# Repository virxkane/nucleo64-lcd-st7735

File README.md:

# nucleo64-lcd-st7735
LCD shield for STM32 Nucleo-64 boards.

This shield is designed for connecting to STM32 Nucleo-64 boards via Arduino<sup>TM</sup> Uno V3.

**WARNING:** Although this shield can be connected to the Arduino<sup>TM</sup> UNO, it is incompatible in logic levels, so it is strictly forbidden to connect this way, otherwise this display will fail!

### Hardware
* The GMT177-01 module is used as a display and is compatible in size and pins. The display controller used is **ST7735**. The display data bus is connected to the hardware SPI. PWM can be used  to control the brightness of the screen backlight.
* Joystick K1-1504SA-03 and one button KLS7-TS6601 can be used for control. Both are connected to 3 General Purpose I/O ports via diodes.
* EEPROM memory M24C08 can be used to store user data. This IC is connected to the I2C hardware bus.
* Two LEDs are connected to ports A0(PA0) and A1(PA1).
* A separate button IT-1187-160GM-G is provided to reset the controller.

### Demo firmware
Two versions of the demo firmware have been written to work on the NUCLEO-F446RE and this shield, one using CMSIS, the other using HAL. Both are under BSD-3-Clause License.
* Using CMSIS: [nucleo-f446re-st7735spi-shield](https://github.com/virxkane/nucleo-f446re-st7735spi-shield)
* Using HAL: [nucleo-f446re-st7735spi-shield-hal](https://github.com/virxkane/nucleo-f446re-st7735spi-shield-hal)

#### Compare performance
| # |  bpp variant  | fill period, ms | transfer period, CMSIS, ms | transfer period, HAL, ms |
|---|---------------|--------|-----------|---------|
| 1 | fb=1, lcd=12  |     3  |      23   |    40   |
| 2 | fb=1, lcd=16  |     3  |      30   |    60   |
| 3 | fb=1, lcd=18  |     3  |      44   |    74   |
| 4 | fb=4, lcd=12  |     3  |      23   |    39   |
| 5 | fb=4, lcd=16  |     3  |      30   |    58   |
| 6 | fb=4, lcd=18  |     3  |      44   |    73   |
| 7 | fb=8, lcd=12  |     2  |      23   |    39   |
| 8 | fb=8, lcd=16  |     2  |      30   |    59   |
| 9 | fb=8, lcd=18  |     2  |      44   |    73   |
| 10 | fb=16, lcd=12 |    3  |      22   |    39   |
| 11 | fb=16, lcd=16 |    3  |      30   |    59   |
| 12 | fb=16, lcd=18 |    3  |      44   |    75   |
| 13 | fb=24, lcd=12 |    3  |      22   |    38   |
| 14 | fb=24, lcd=16 |    3  |      30   |    61   |
| 15 | fb=24, lcd=18 |    3  |      44   |    73   |

Where *fb* - frame buffer color depth, *lcd* - LCD module color depth, *fill period* - frame buffer fill period, *transfer period* - period of frame buffer transmission to LCD module.

Tests performed at SPI clock 11,25 Mbits/s.

### Schematic

### Some photo
Unfortunately, there are currently no rev.4 boards, and the existing rev.3 boards have a small error - the LEDs are connected to RX/D0(PA3) and TX/D1(PA2), which by default are connected to the USART of the on-board ST-LINK/V2-1 programmer. To correct this drawback, two wire are placed on the bottom of the board to ports A0(PA0) and A1(PA1). The boards of the rev.4 are free from this drawback.

#### Front view (rev.3)

#### Back view (rev.3)

#### Paired with NUCLEO-F446RE with running [demo](https://github.com/virxkane/nucleo-f446re-st7735spi-shield) (rev.3)

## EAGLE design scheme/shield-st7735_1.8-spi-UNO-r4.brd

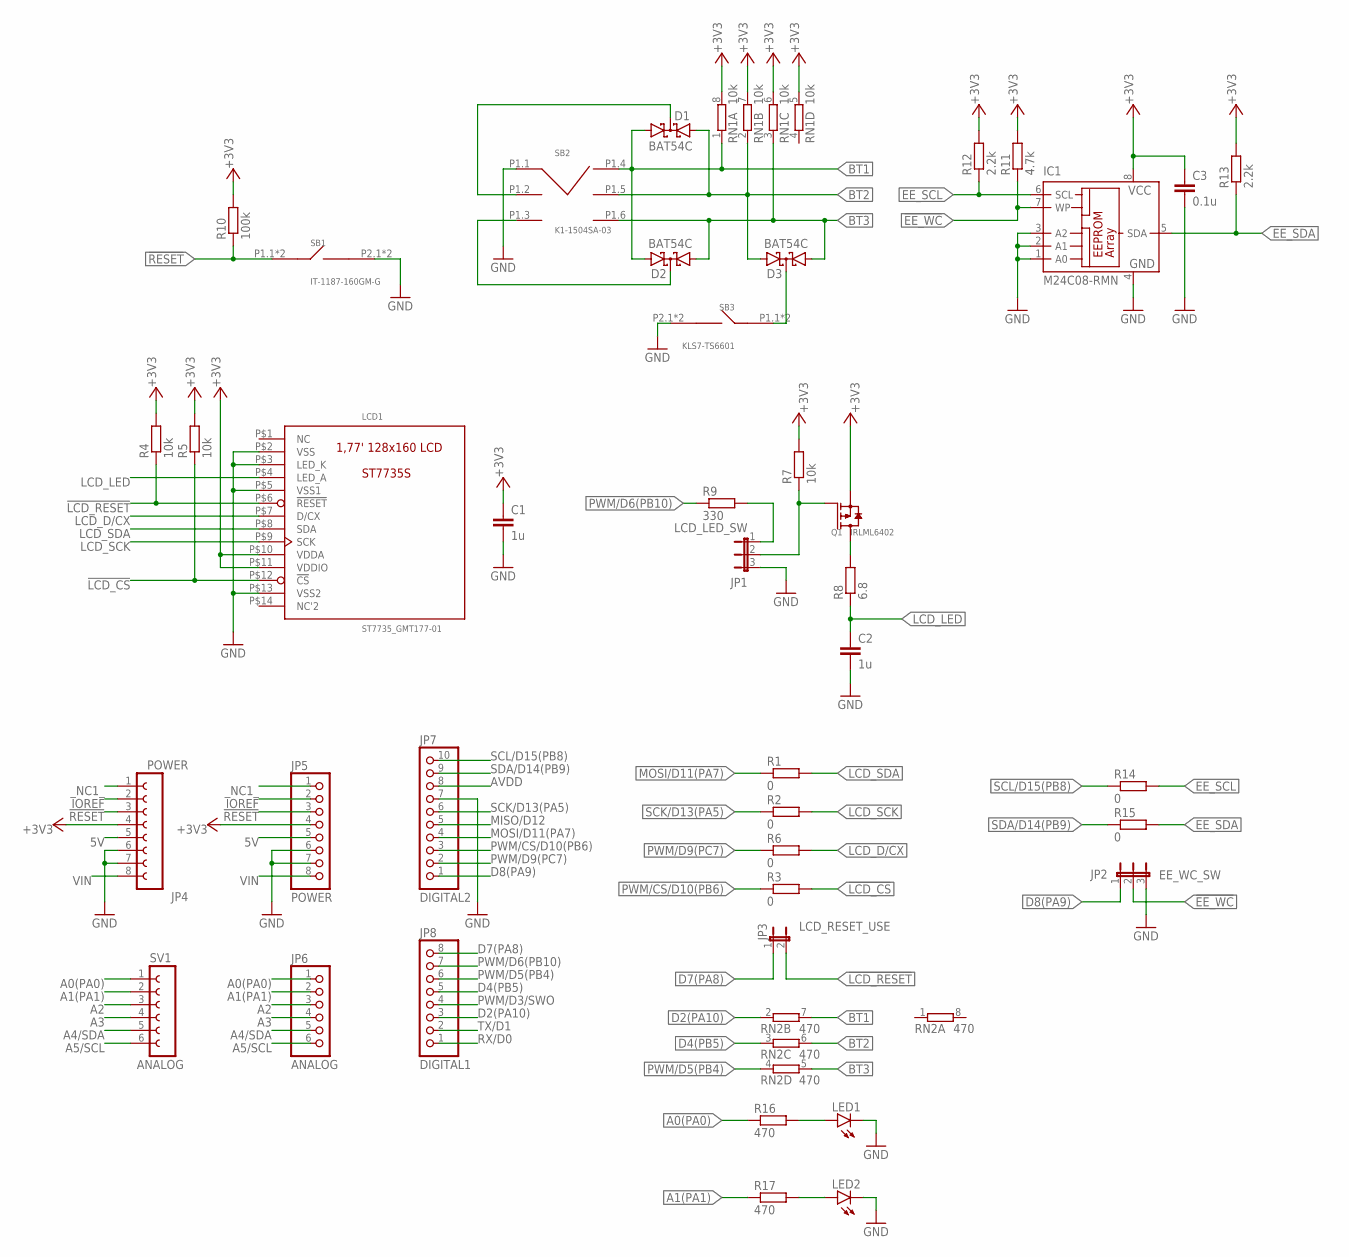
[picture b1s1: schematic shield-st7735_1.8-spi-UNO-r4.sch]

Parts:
C1, C2: 1u; C1206
C3: 0.1u; C1206
D1, D2, D3: BAT54C; SOT23
IC1: M24C08-RMN; SO-08
JP1: LCD_LED_SW; JP2
JP2: EE_WC_SW; JP2
JP3: LCD_RESET_USE; JP1
JP4: POWER; FE08
JP5: POWER; 1X08
JP6: ANALOG; 1X06
JP7: DIGITAL2; 1X10
JP8: DIGITAL1; 1X08
LCD1: ST7735_GMT177-01; GMT177-01
LED1, LED2: LEDCHIP-LED0805; CHIP-LED0805
Q1: IRLML6402; SOT23
R1, R2, R3, R6, R14, R15: 0; R1206
R4, R5, R7: 10k; R1206
R8: 6.8; R1206
R9: 330; R1206
R10: 100k; R1206
R11: 4.7k; R1206
R12, R13: 2.2k; R1206
R16, R17: 470; R1206
RN1: 10k; EXB38V
RN2: 470; EXB38V
SB1: IT-1187-160GM-G
SB2: K1-1504SA-03; K1-1504SA-3
SB3: KLS7-TS6601
SV1: ANALOG; FE06

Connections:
5V: JP4.5, JP5.5
!EE_WC!: IC1.7 (WP), JP2.2, R11.1
!LCD_CS!: LCD1.P$12 (!CS!), R3.2, R5.1
!LCD_RESET!: JP3.2, LCD1.P$6 (!RESET!), R4.1
!RESET!: JP4.3, JP5.3, R10.1, SB1.P1.1 (P1), SB1.P1.2 (P1)
+3V3: C1.1, C3.1, IC1.8 (VCC), JP4.4, JP5.4, LCD1.P$10 (VDDA), LCD1.P$11 (VDDIO), Q1.2 (S), R4.2, R5.2, R7.2, R10.2, R11.2, R12.2, R13.2, RN1.5 (2), RN1.6 (2), RN1.7 (2), RN1.8 (2)
A0(PA0): JP6.1, R16.1, SV1.1
A1(PA1): JP6.2, R17.1, SV1.2
A2: JP6.3, SV1.3
A3: JP6.4, SV1.4
A4/SDA: JP6.5, SV1.5
A5/SCL: JP6.6, SV1.6
AVDD: JP7.8
BT1: D1.1 (A1), D2.2 (A2), RN1.1, RN2.7 (2), SB2.P1.4 (P4)
BT2: D1.2 (A2), D3.2 (A2), RN1.2 (1), RN2.6 (2), SB2.P1.5 (P5)
BT3: D2.1 (A1), D3.1 (A1), RN1.3 (1), RN2.5 (2), SB2.P1.6 (P6)
D2(PA10): JP8.3, RN2.2 (1)
D4(PB5): JP8.5, RN2.3 (1)
D7(PA8): JP3.1, JP8.8
D8(PA9): JP2.1, JP7.1
EE_SCL: IC1.6 (SCL), R12.1, R14.2
EE_SDA: IC1.5 (SDA), R13.1, R15.2
GND: C1.2, C2.2, C3.2, IC1.1 (A0), IC1.2 (A1), IC1.3 (A2), IC1.4 (GND), JP1.3, JP2.3, JP4.6, JP4.7, JP5.6, JP5.7, JP7.7, LCD1.P$2 (VSS), LCD1.P$3 (LED_K), LCD1.P$5 (VSS1), LCD1.P$13 (VSS2), LED1.C, LED2.C, SB1.P2.1 (P2), SB1.P2.2 (P2), SB2.P1.1 (P1), SB3.P2.1 (P2), SB3.P2.2 (P2)
IOREF: JP4.2, JP5.2
LCD_D/CX: LCD1.P$7 (D/CX), R6.2
LCD_LED: C2.1, LCD1.P$4 (LED_A), R8.1
LCD_SCK: LCD1.P$9 (SCK), R2.2
LCD_SDA: LCD1.P$8 (SDA), R1.2
MISO/D12: JP7.5
MOSI/D11(PA7): JP7.4, R1.1
unnamed: JP1.2, Q1.1 (G), R7.1
unnamed: Q1.3 (D), R8.2
unnamed: D2.3 (CC), SB2.P1.3 (P3)
unnamed: JP1.1, R9.2
unnamed: D1.3 (CC), SB2.P1.2 (P2)
unnamed: D3.3 (CC), SB3.P1.1 (P1), SB3.P1.2 (P1)
unnamed: LED2.A, R17.2
unnamed: LED1.A, R16.2
PWM/CS/D10(PB6): JP7.3, R3.1
PWM/D3/SWO: JP8.4
PWM/D5(PB4): JP8.6, RN2.4 (1)
PWM/D6(PB10): JP8.7, R9.1
PWM/D9(PC7): JP7.2, R6.1
RX/D0: JP8.1
SCK/D13(PA5): JP7.6, R2.1
SCL/D15(PB8): JP7.10, R14.1
SDA/D14(PB9): JP7.9, R15.1
TX/D1: JP8.2
VIN: JP4.8, JP5.8
_NC1_: JP4.1, JP5.1

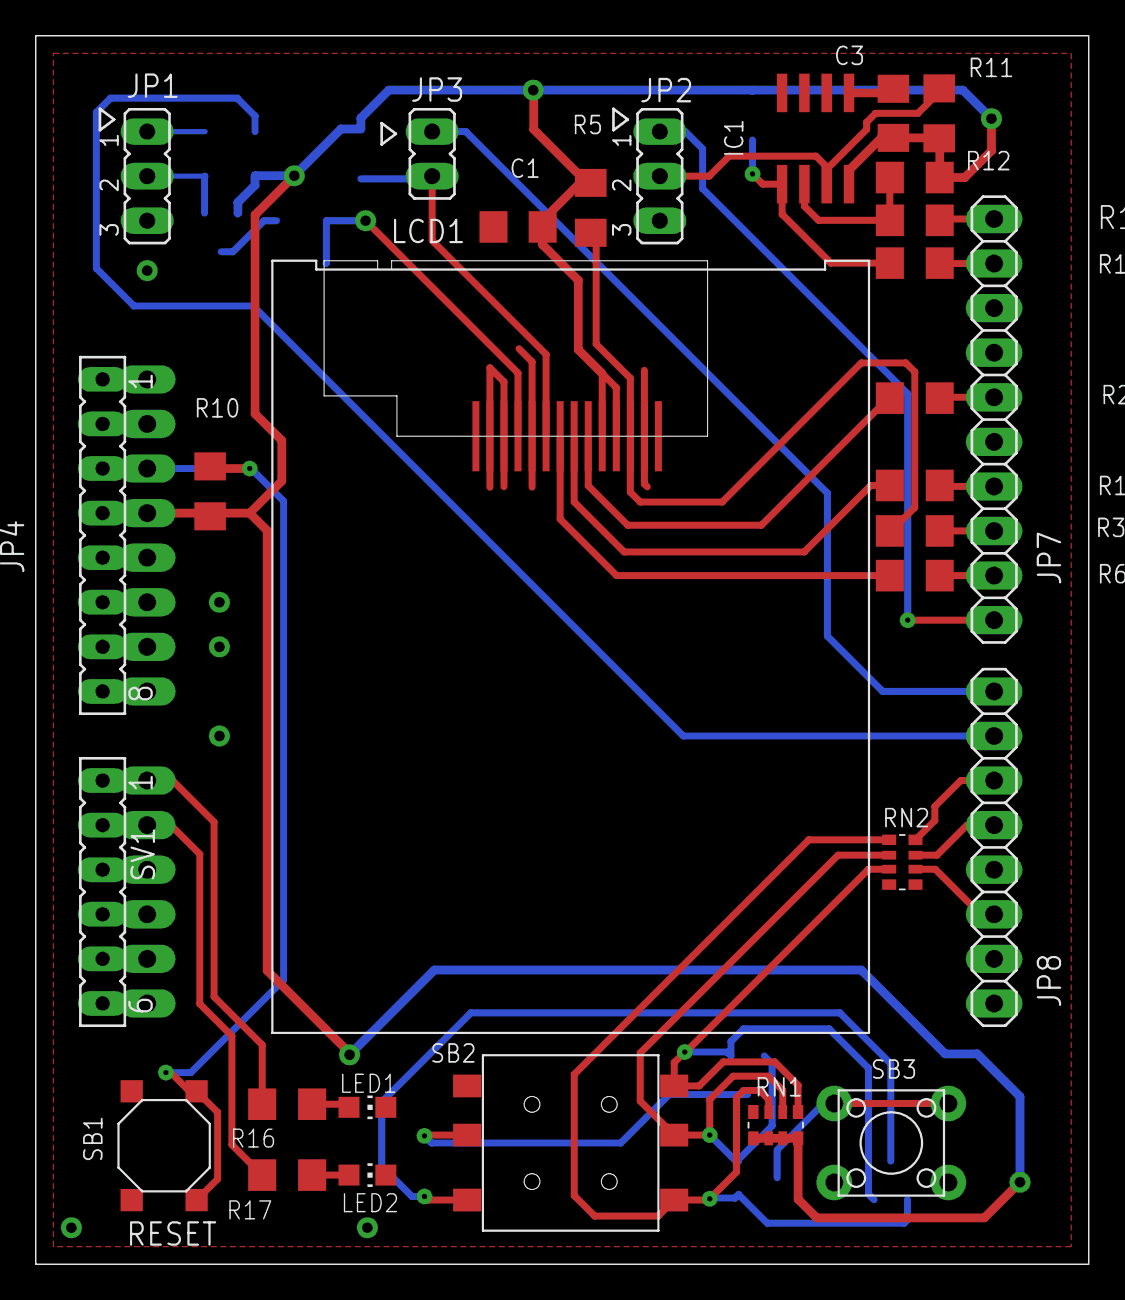
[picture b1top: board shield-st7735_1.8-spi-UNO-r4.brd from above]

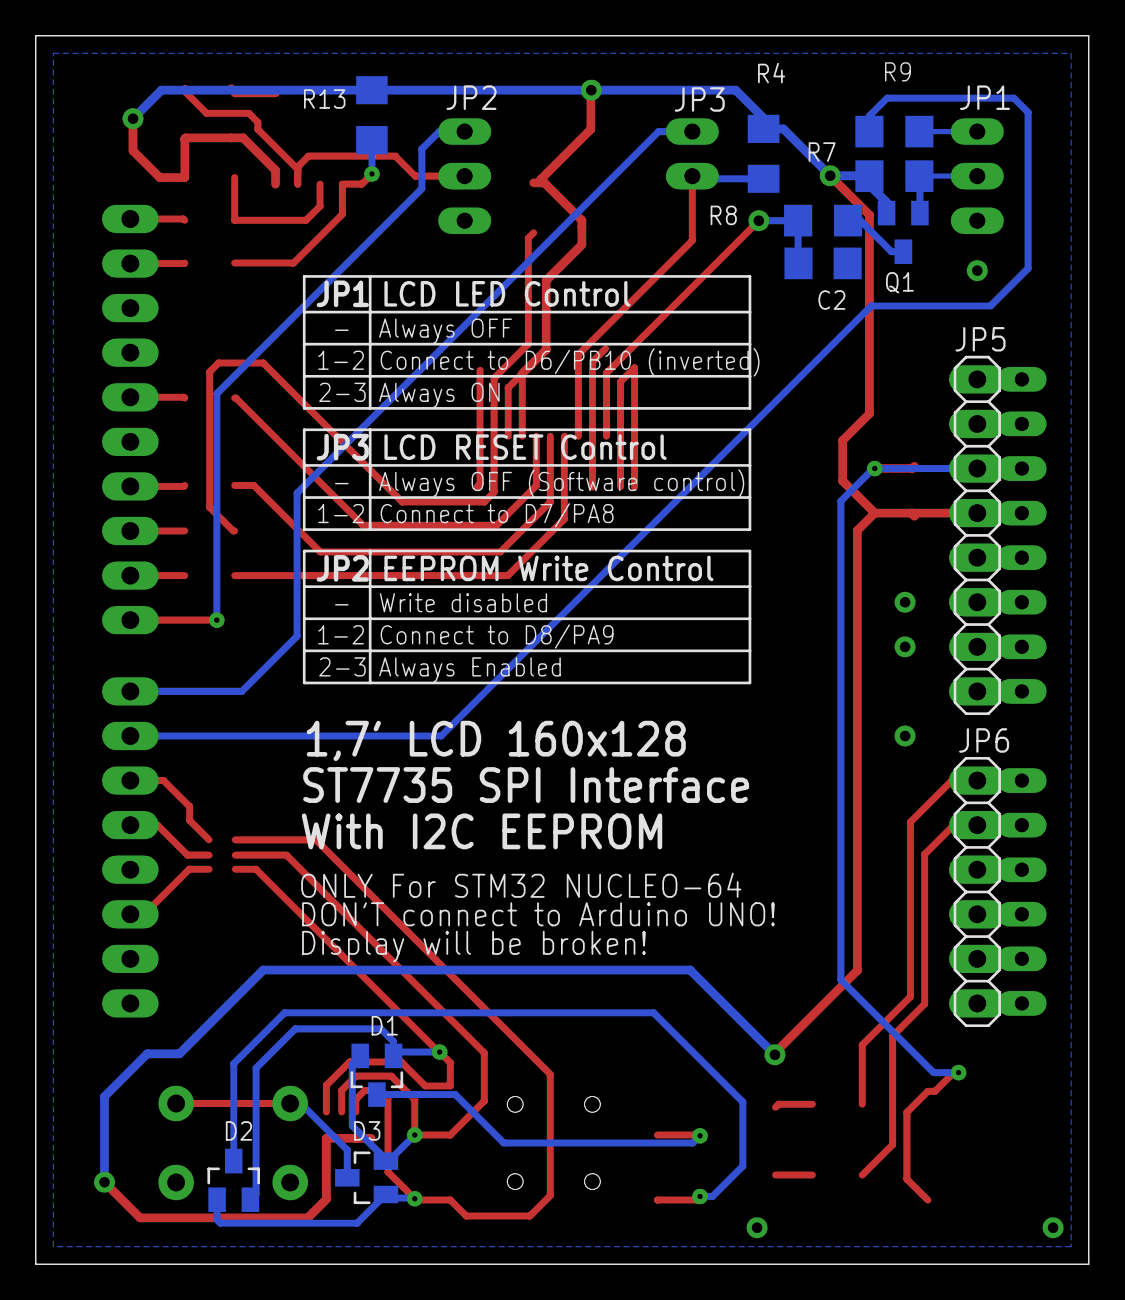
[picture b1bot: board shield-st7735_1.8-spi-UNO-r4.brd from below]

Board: 2 copper layers, 60.0 x 70.0 mm, 42 parts (12 on the bottom side), 45 nets.

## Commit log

2021-11-02 Add schematic.
2021-11-02 Added schematic in image format.
2021-11-02 Added photo for patched rev.3
2023-09-10 New revision, the project has been remade in KiCAD.
